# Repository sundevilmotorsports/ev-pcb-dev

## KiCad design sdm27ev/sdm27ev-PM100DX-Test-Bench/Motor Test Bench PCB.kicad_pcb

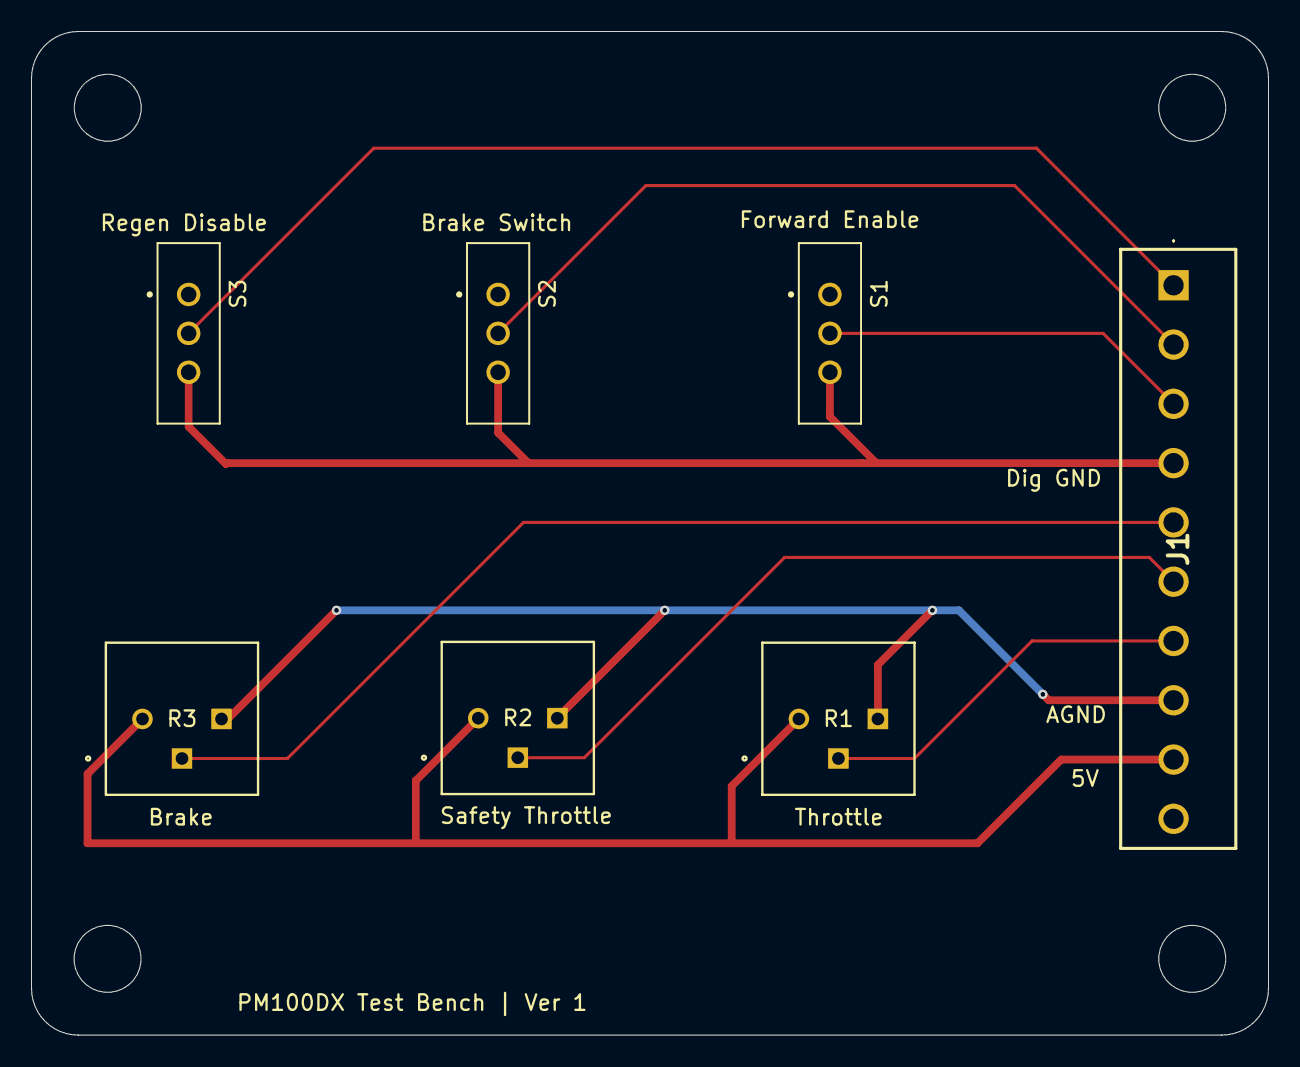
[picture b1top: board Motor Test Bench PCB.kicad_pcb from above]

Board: 2 copper layers, 79.5 x 64.5 mm, 7 parts (0 on the bottom side), 9 nets.

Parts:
J1: 20020327-D101B01LF; 20020327D101B01LF
R1: Throttle; POT_3386P
R2: Safety Throttle; POT_3386P
R3: Brake; POT_3386P
S1: Forward Enable; SW_EG1218
S2: Brake Switch; SW_EG1218
S3: Regen Disable; SW_EG1218

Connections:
5V: J1.9, R1.1, R2.1, R3.1
AGND: J1.8, R1.3, R2.3, R3.3
Brake Signal: J1.5, R3.2
Brake Switch: J1.2, S2.2
Digintal GND: J1.4, S1.3, S2.3, S3.3
Forward Enable: J1.3, S1.2
Regen Disable: J1.1, S3.2
Safety Throttle Signal: J1.6, R2.2
Throttle Signal: J1.7, R1.2

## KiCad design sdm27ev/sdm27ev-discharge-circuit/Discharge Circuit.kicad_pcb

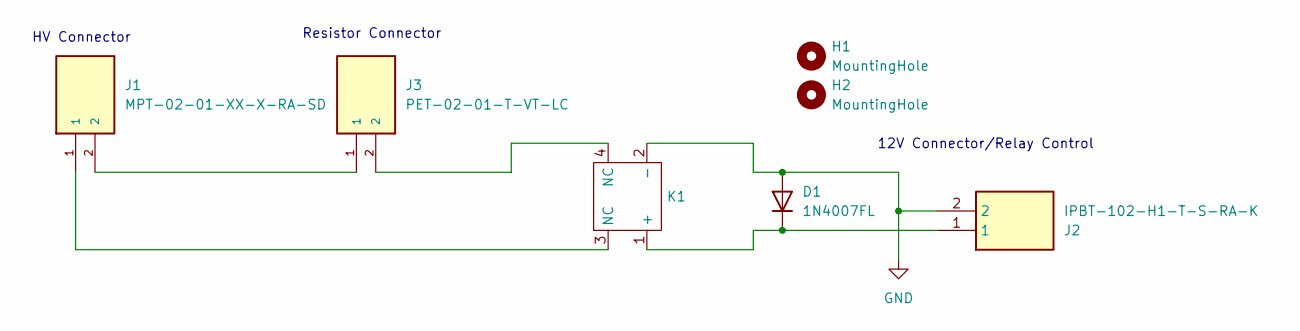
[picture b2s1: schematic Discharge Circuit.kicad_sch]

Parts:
D1: 1N4007FL; D_SOD-123F
H1, H2: MountingHole; MountingHole_3.2mm_M3
J1: MPT-02-01-XX-X-RA-SD; SAMTEC_MPT-02-01-XX-X-RA-SD; PARTREV B
J2: IPBT-102-H1-T-S-RA-K; IPBT102H1TSRAK; Mouser Part Number 200-IPBT102H1TSRAK
J3: PET-02-01-T-VT-LC; SAMTEC_PET-02-XX-X-VT-LC; PARTREV C
K1: S82405VHR

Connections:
GND: D1.2 (A), J2.2, K1.2 (-)
unnamed: D1.1 (K), J2.1, K1.1 (+)
unnamed: J1.1, K1.3 (NC)
unnamed: J1.2, J3.1
unnamed: J3.2, K1.4 (NC)

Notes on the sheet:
Resistor Connector
12V Connector/Relay Control
HV Connector

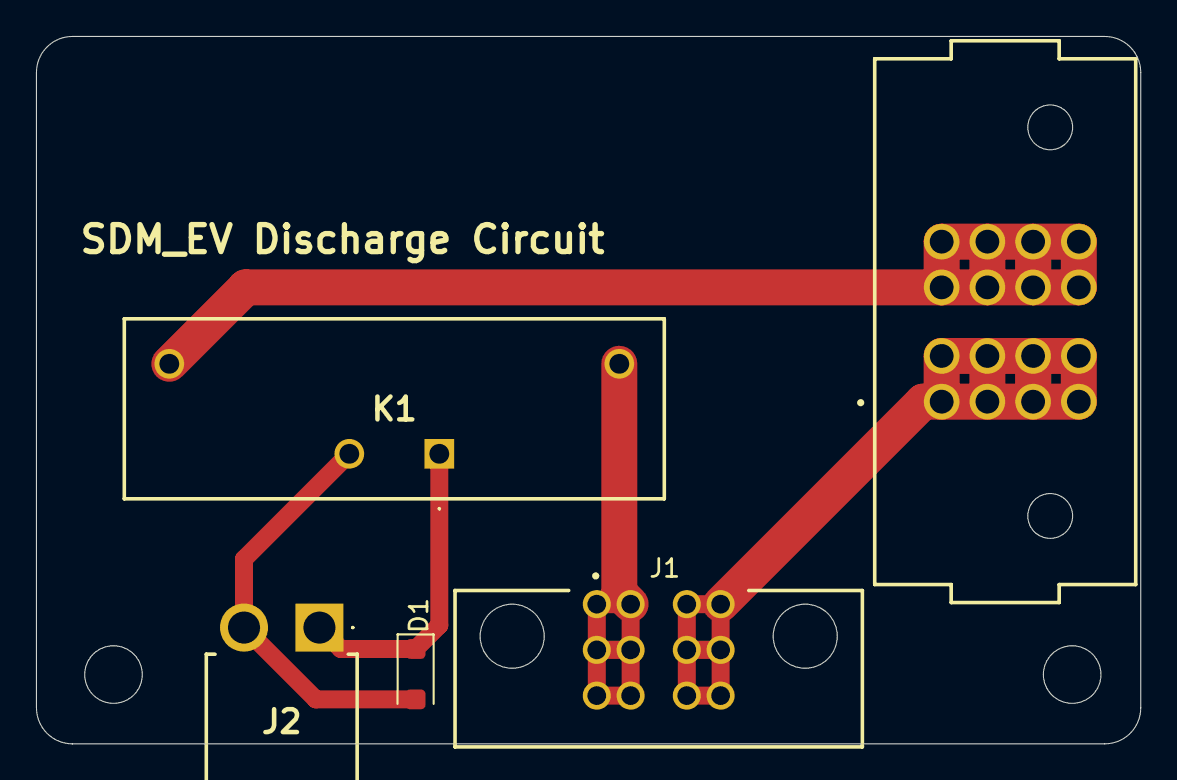
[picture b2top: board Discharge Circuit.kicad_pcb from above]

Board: 2 copper layers, 61.3 x 39.3 mm, 7 parts (0 on the bottom side), 5 nets.

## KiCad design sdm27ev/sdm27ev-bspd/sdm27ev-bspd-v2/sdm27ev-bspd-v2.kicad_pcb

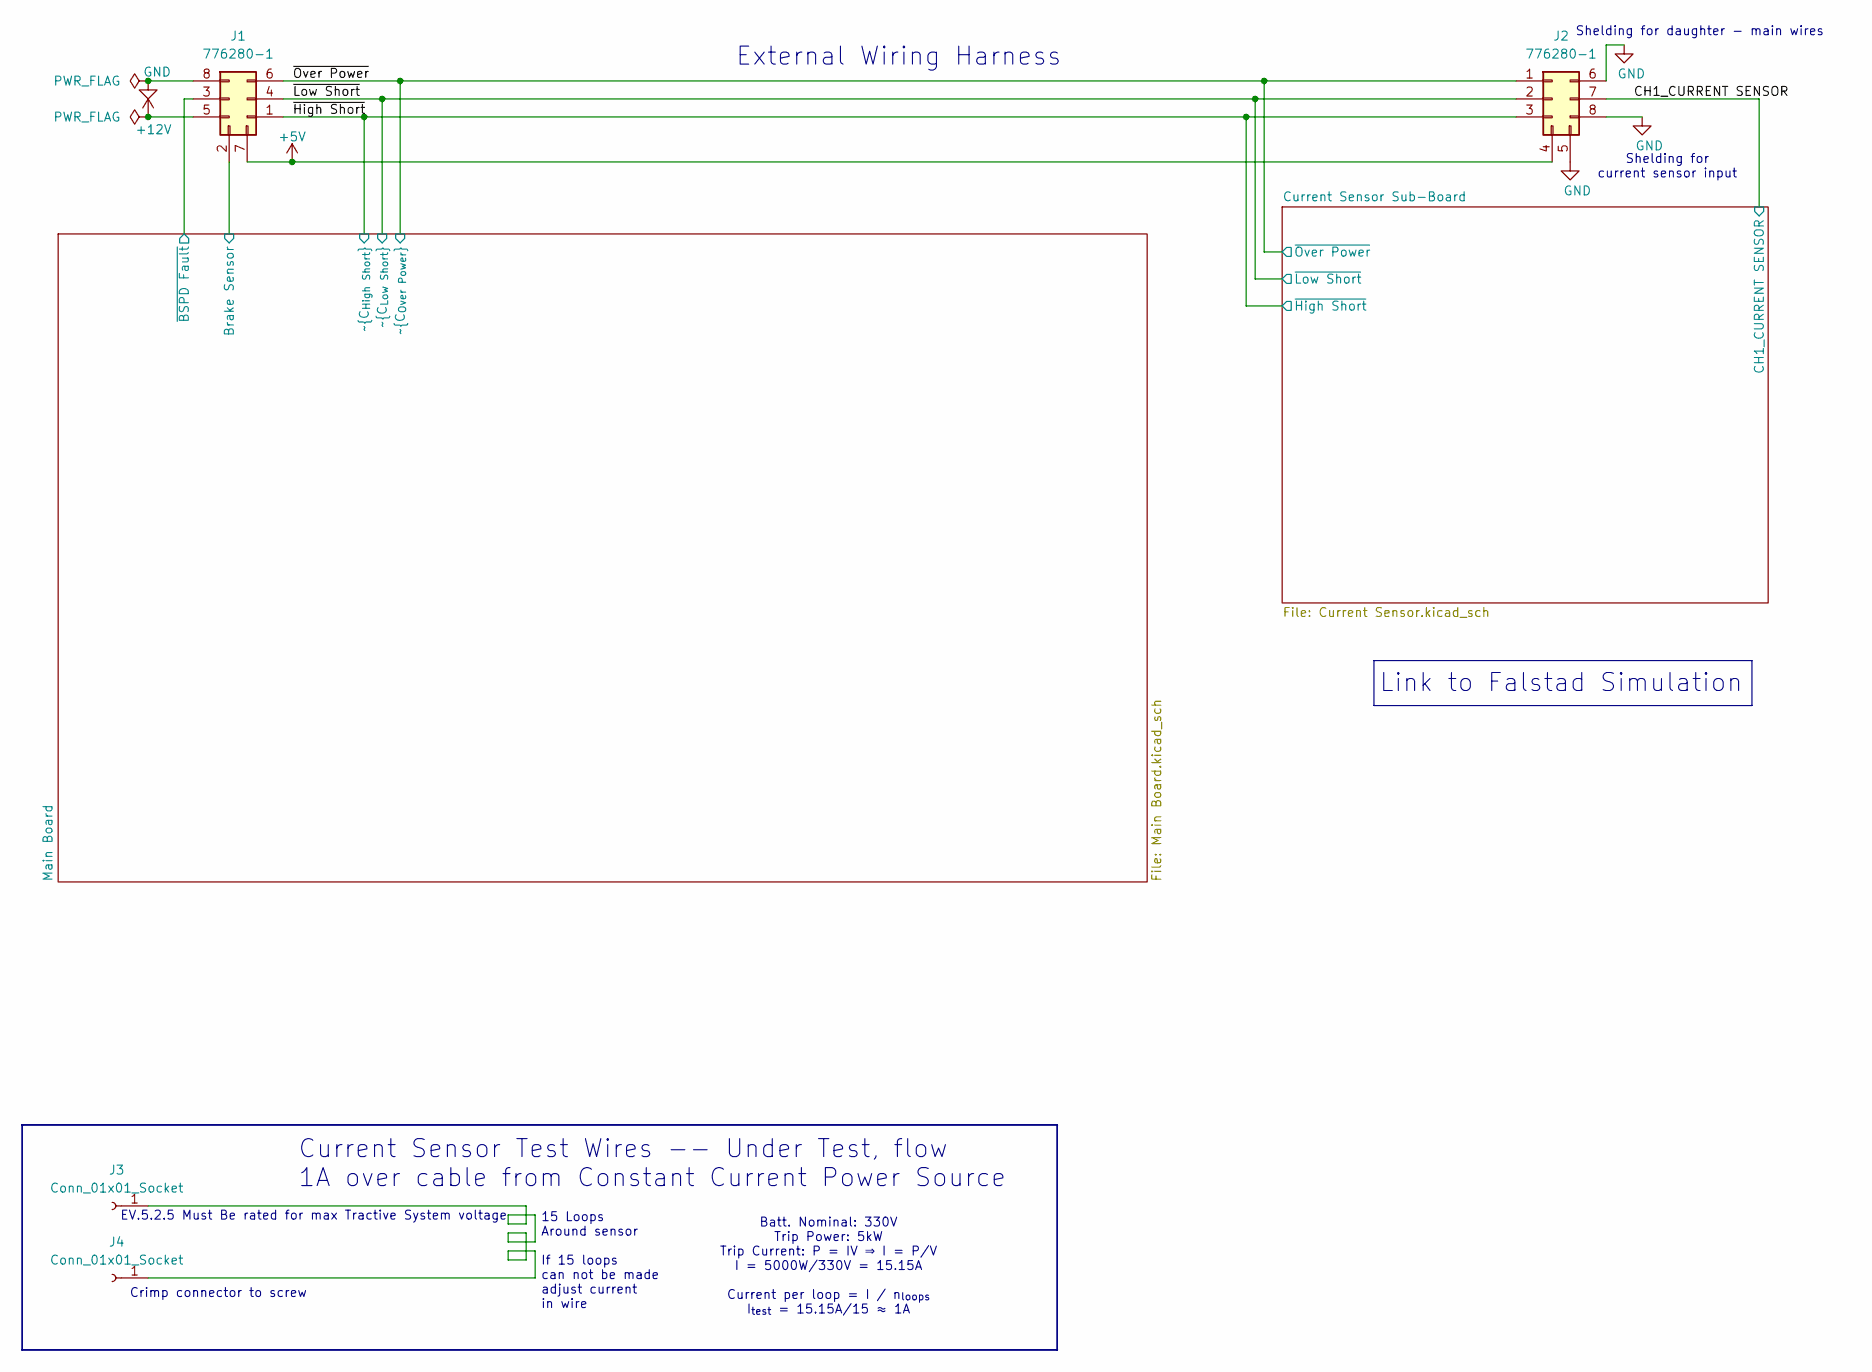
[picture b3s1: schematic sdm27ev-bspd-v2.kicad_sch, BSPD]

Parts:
J1, J2: 776280-1; Mouser Part Number 571-776280-1
J3, J4: Conn_01x01_Socket

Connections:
+5V: J1.7 (Pin_5), J2.4; also elsewhere on the board
+12V: J1.5 (Pin_3); also elsewhere on the board
/CH1_CURRENT SENSOR: J2.7; also elsewhere on the board
/Main Board/brake: J1.2 (Pin_4); also elsewhere on the board
/Main Board/~BSPD Fault: J1.3 (Pin_2); also elsewhere on the board
/~High Short: J1.1 (Pin_8), J2.3; also elsewhere on the board
/~Low Short: J1.4 (Pin_7), J2.2; also elsewhere on the board
/~Over Power: J1.6, J2.1; also elsewhere on the board
GND: J1.8 (Pin_1), J2.5, J2.6, J2.8; also elsewhere on the board
unnamed: J3.1, J4.1

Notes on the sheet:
External Wiring Harness
Batt. Nominal: 330V Trip Power: 5kW Trip Current: P = IV ⇒ I = P/V I = 5000W/330V = 15.15A Current per loop = I / n_{loops} I_{test} = 15.15A/15 ≈ 1A
15 Loops Around sensor If 15 loops can not be made adjust current in wire
Crimp connector to screw
EV.5.2.5 Must Be rated for max Tractive System voltage
Current Sensor Test Wires -- Under Test, flow 1A over cable from Constant Current Power Source
Shelding for daughter - main wires
Shelding for current sensor input
Link to Falstad Simulation

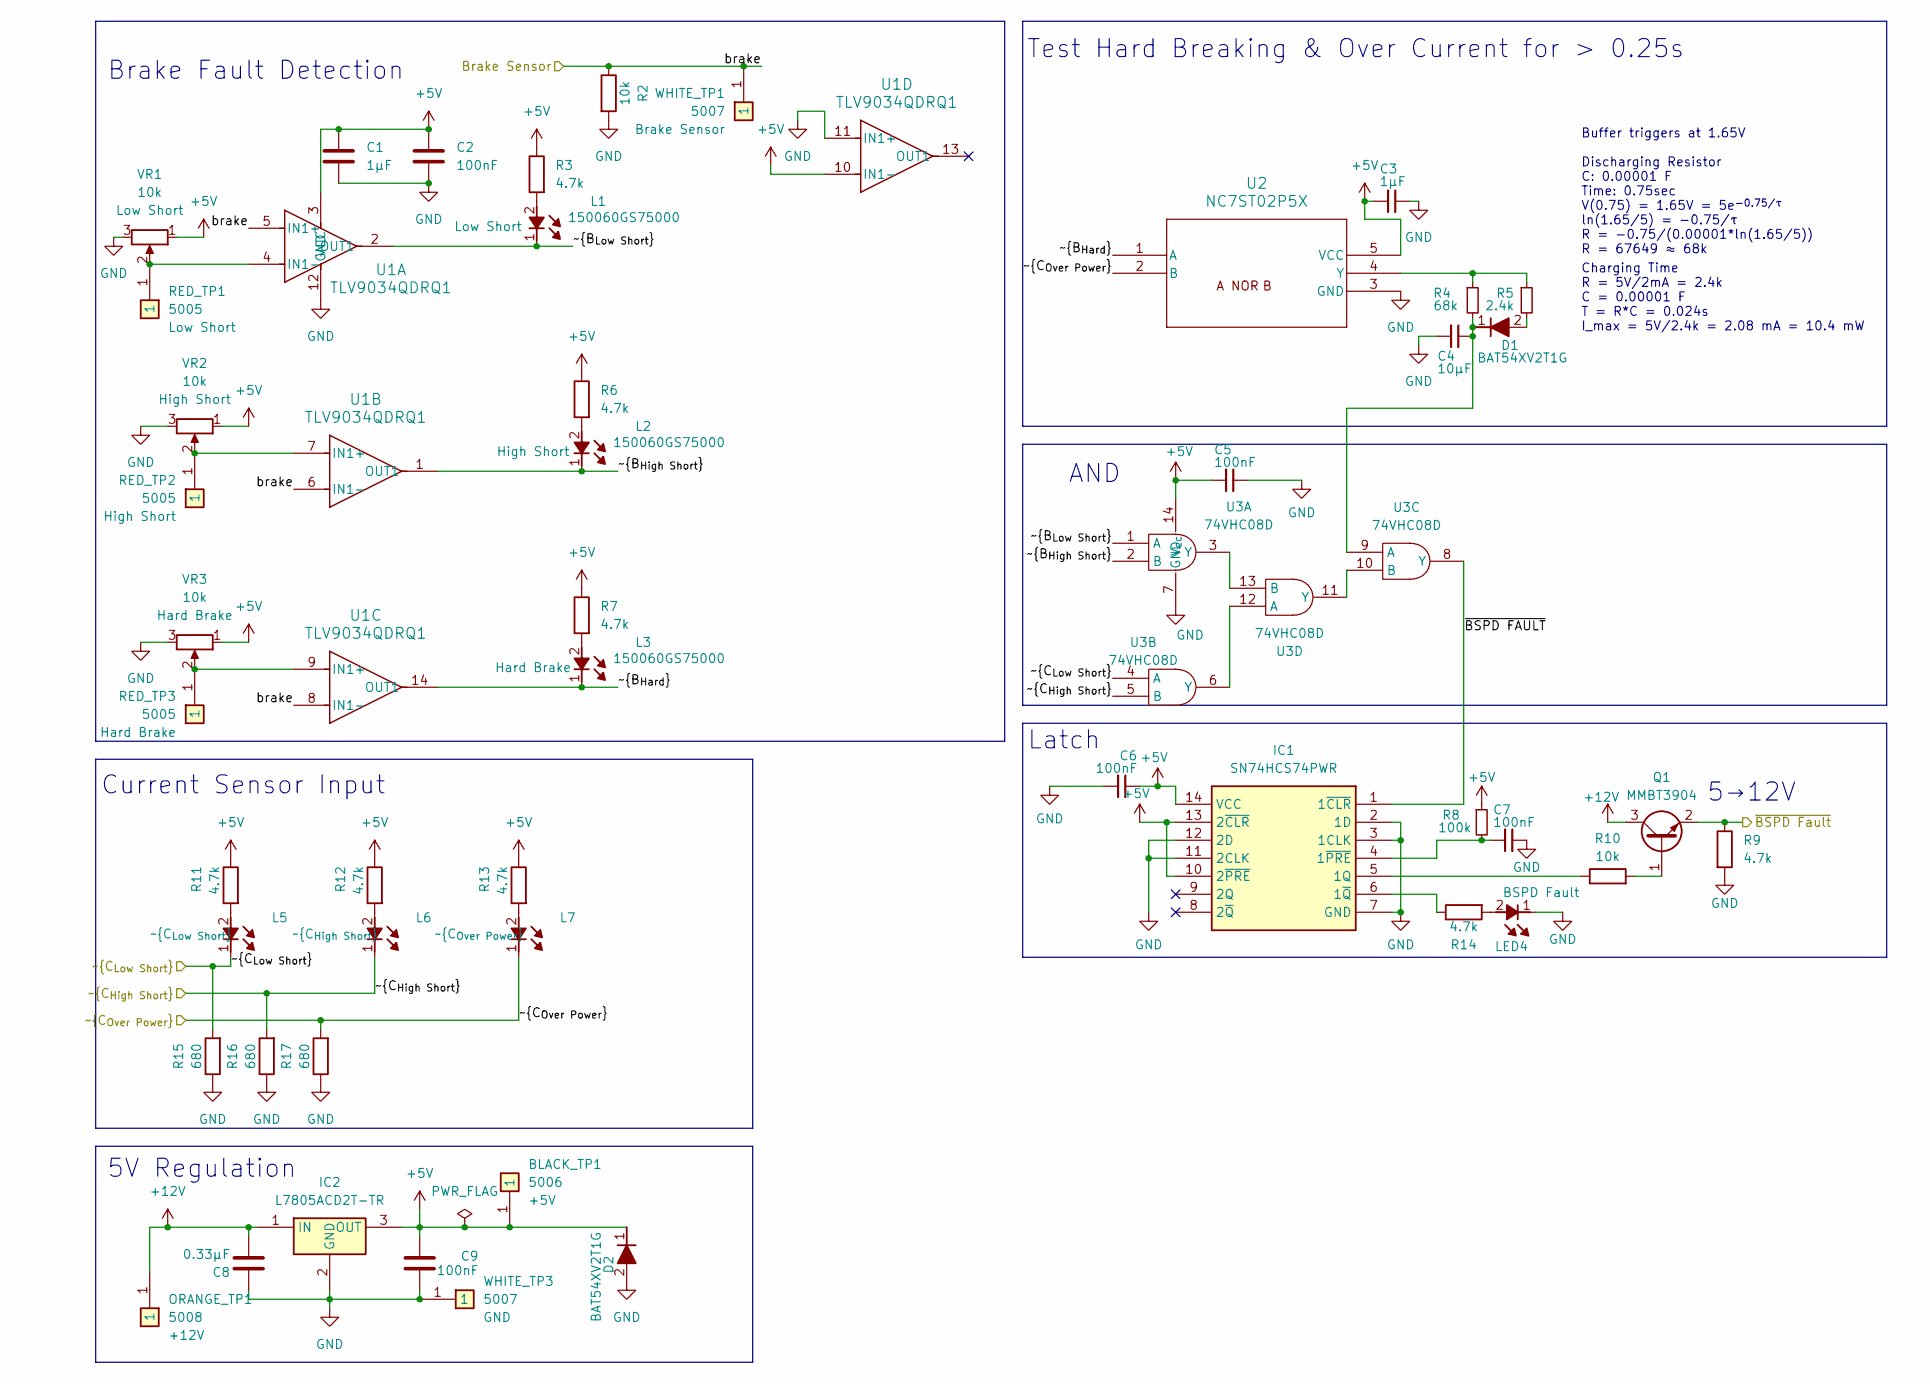
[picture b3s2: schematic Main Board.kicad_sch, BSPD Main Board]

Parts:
BLACK_TP1: 5006; Mouser Part Number 534-5006
C1, C3: 1µF; C_0603_1608Metric
C2, C5, C6, C7, C9: 100nF; C_0603_1608Metric
C4: 10µF; C_0603_1608Metric
C8: 0.33µF; C_0603_1608Metric
D1, D2: BAT54XV2T1G; SODFL1608X70N; Mouser Part Number 863-BAT54XV2T1G
IC1: SN74HCS74PWR; Mouser Part Number 595-SN74HCS74PWR
IC2: L7805ACD2T-TR; L7805ACD2TTR; Mouser Part Number 511-L7805ACD2T-TR
L1, L2, L3, L5, L6, L7: 150060GS75000; LEDC1608X80N; Mouser Part Number 710-150060GS75000
LED4: 150060GS75000; LEDC1608X80N; Mouser Part Number 710-150060GS75000
ORANGE_TP1: 5008; 5005; Mouser Part Number 534-5008
Q1: MMBT3904; SOT-23
R2, R10: 10k; R_0603_1608Metric
R3, R6, R7, R9, R11, R12, R13, R14: 4.7k; R_0603_1608Metric
R4: 68k; R_0603_1608Metric
R5: 2.4k; R_0603_1608Metric
R8: 100k; R_0603_1608Metric
R15, R16, R17: 680; R_0603_1608Metric
RED_TP1, RED_TP2, RED_TP3: 5005; Mouser Part Number 534-5005
U1: TLV9034QDRQ1; SOIC-14_3.9x8.7mm_P1.27mm
U2: NC7ST02P5X; SC-88A-5_1P35X2P2_ONS
U3: 74VHC08D
VR1, VR2, VR3: 10k; 3386P1103TLF; Mouser Part Number 652-3386P-1-103TLF
WHITE_TP1, WHITE_TP3: 5007; Mouser Part Number 534-5007

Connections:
+5V: BLACK_TP1.1 (1_1), C1.1, C2.1, C3.1, C5.2, C6.2, C9.2, D2.1 (K), IC1.10 (2~PRE), IC1.13 (2~CLR), IC1.14 (VCC), IC2.3 (OUT), R3.1, R6.1, R7.1, R8.1, R11.1, R12.1, R13.1, U1.3 (VCC), U1.10 (IN1-), U2.5 (VCC), U3.14 (V_{cc}), VR1.1 (CCW), VR2.1 (CCW), VR3.1 (CCW); also elsewhere on the board
+12V: C8.2, IC2.1 (IN), ORANGE_TP1.1 (1_1), Q1.3 (C); also elsewhere on the board
/Main Board/brake: R2.1, U1.5 (IN1+), U1.6 (IN1-), U1.8 (IN1-), WHITE_TP1.1 (1_1); also elsewhere on the board
/Main Board/~BSPD FAULT: IC1.1 (1~CLR), U3.8 (Y)
/Main Board/~BSPD Fault: Q1.2 (E), R9.1; also elsewhere on the board
/Main Board/~B_{Hard}: L3.1 (K), U1.14 (OUT1), U2.1 (A)
/Main Board/~B_{High Short}: L2.1 (K), U1.1 (OUT1), U3.2 (B)
/Main Board/~B_{Low Short}: L1.1 (K), U1.2 (OUT1), U3.1 (A)
/~High Short: L6.1 (K), R16.2, U3.5 (B); also elsewhere on the board
/~Low Short: L5.1 (K), R15.2, U3.4 (A); also elsewhere on the board
/~Over Power: L7.1 (K), R17.2, U2.2 (B); also elsewhere on the board
GND: C1.2, C2.2, C3.2, C4.2, C5.1, C6.1, C7.1, C8.1, C9.1, D2.2 (A), IC1.2 (1D), IC1.3 (1CLK), IC1.7 (GND), IC1.11 (2CLK), IC1.12 (2D), IC2.2 (GND), LED4.1 (K), R2.2, R9.2, R15.1, R16.1, R17.1, U1.11 (IN1+), U1.12 (GND), U2.3 (GND), U3.7 (GND), VR1.3 (CW), VR2.3 (CW), VR3.3 (CW), WHITE_TP3.1 (1_1); also elsewhere on the board
unnamed: D1.2 (A), R5.2
unnamed: C4.1, D1.1 (K), R4.2, U3.9 (A)
unnamed: IC1.5 (1Q), R10.1
unnamed: C7.2, IC1.4 (1~PRE), R8.2
unnamed: IC1.6 (1~Q), R14.1
unnamed: L1.2 (A), R3.2
unnamed: L2.2 (A), R6.2
unnamed: L3.2 (A), R7.2
unnamed: L5.2 (A), R11.2
unnamed: L6.2 (A), R12.2
unnamed: L7.2 (A), R13.2
unnamed: LED4.2 (A), R14.2
unnamed: Q1.1 (B), R10.2
unnamed: RED_TP1.1 (1_1), U1.4 (IN1-), VR1.2 (Wiper)
unnamed: RED_TP2.1 (1_1), U1.7 (IN1+), VR2.2 (Wiper)
unnamed: RED_TP3.1 (1_1), U1.9 (IN1+), VR3.2 (Wiper)
unnamed: R4.1, R5.1, U2.4 (Y)
unnamed: U3.3 (Y), U3.13 (B)
unnamed: U3.6 (Y), U3.12 (A)
unnamed: U3.10 (B), U3.11 (Y)

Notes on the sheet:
Brake Fault Detection
AND
Test Hard Breaking & Over Current for > 0.25s
5→12V
Current Sensor Input
Charging Time R = 5V/2mA = 2.4k C = 0.00001 F T = R*C = 0.024s I_max = 5V/2.4k = 2.08 mA = 10.4 mW
5V Regulation
Buffer triggers at 1.65V Discharging Resistor C: 0.00001 F Time: 0.75sec V(0.75) = 1.65V = 5e^{-0.75/τ} ln(1.65/5) = -0.75/τ R = -0.75/(0.00001*ln(1.65/5)) R = 67649 ≈ 68k
Latch

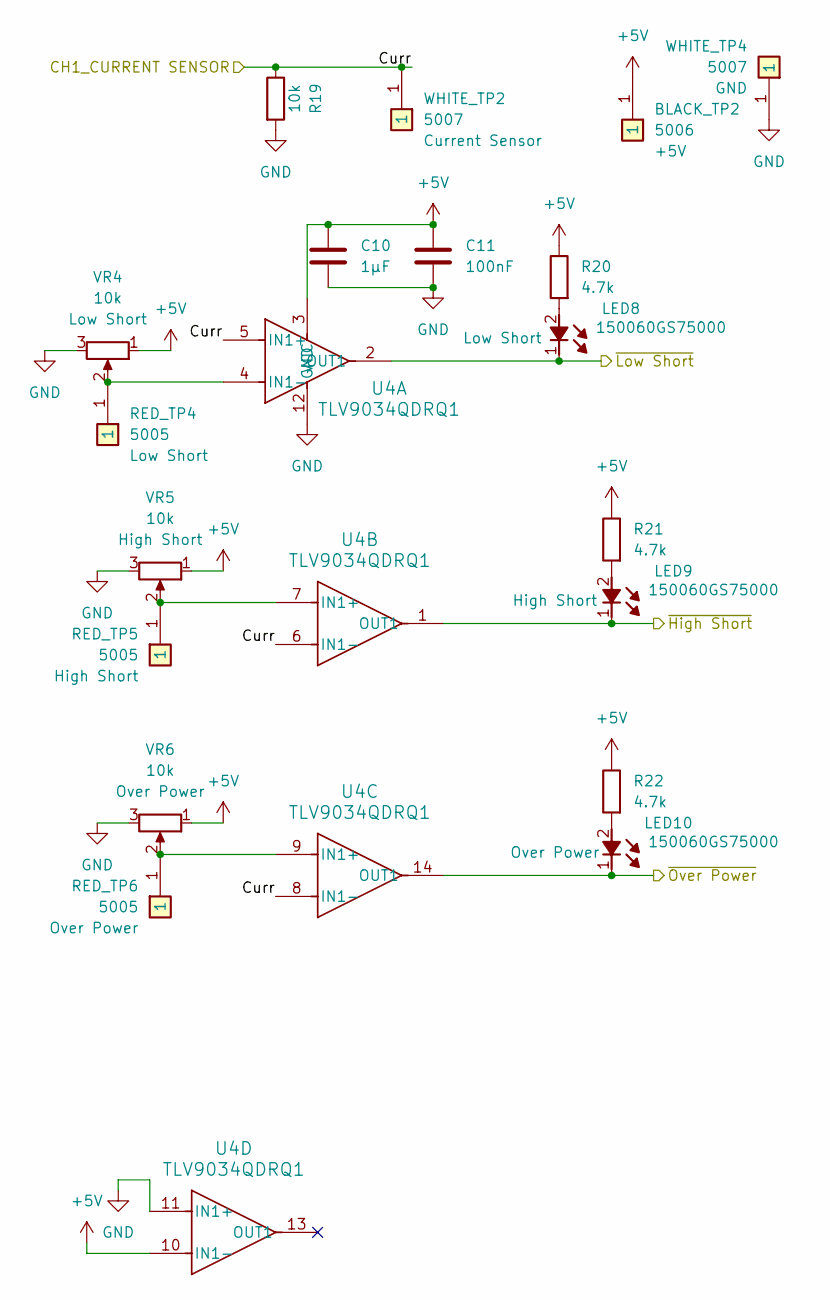
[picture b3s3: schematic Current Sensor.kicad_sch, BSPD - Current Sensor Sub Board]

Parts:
BLACK_TP2: 5006; Mouser Part Number 534-5006
C10: 1µF; C_0603_1608Metric
C11: 100nF; C_0603_1608Metric
LED8, LED9, LED10: 150060GS75000; LEDC1608X80N; Mouser Part Number 710-150060GS75000
R19: 10k; R_0603_1608Metric
R20, R21, R22: 4.7k; R_0603_1608Metric
RED_TP4, RED_TP5, RED_TP6: 5005; Mouser Part Number 534-5005
U4: TLV9034QDRQ1; SOIC-14_3.9x8.7mm_P1.27mm
VR4, VR5, VR6: 10k; 3386P1103TLF; Mouser Part Number 652-3386P-1-103TLF
WHITE_TP2, WHITE_TP4: 5007; Mouser Part Number 534-5007

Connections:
+5V: BLACK_TP2.1 (1_1), C10.1, C11.1, R20.1, R21.1, R22.1, U4.3 (VCC), U4.10 (IN1-), VR4.1 (CCW), VR5.1 (CCW), VR6.1 (CCW); also elsewhere on the board
/CH1_CURRENT SENSOR: R19.1, U4.5 (IN1+), U4.6 (IN1-), U4.8 (IN1-), WHITE_TP2.1 (1_1); also elsewhere on the board
/~High Short: LED9.1 (K), U4.1 (OUT1); also elsewhere on the board
/~Low Short: LED8.1 (K), U4.2 (OUT1); also elsewhere on the board
/~Over Power: LED10.1 (K), U4.14 (OUT1); also elsewhere on the board
GND: C10.2, C11.2, R19.2, U4.11 (IN1+), U4.12 (GND), VR4.3 (CW), VR5.3 (CW), VR6.3 (CW), WHITE_TP4.1 (1_1); also elsewhere on the board
unnamed: LED8.2 (A), R20.2
unnamed: LED9.2 (A), R21.2
unnamed: LED10.2 (A), R22.2
unnamed: RED_TP4.1 (1_1), U4.4 (IN1-), VR4.2 (Wiper)
unnamed: RED_TP5.1 (1_1), U4.7 (IN1+), VR5.2 (Wiper)
unnamed: RED_TP6.1 (1_1), U4.9 (IN1+), VR6.2 (Wiper)

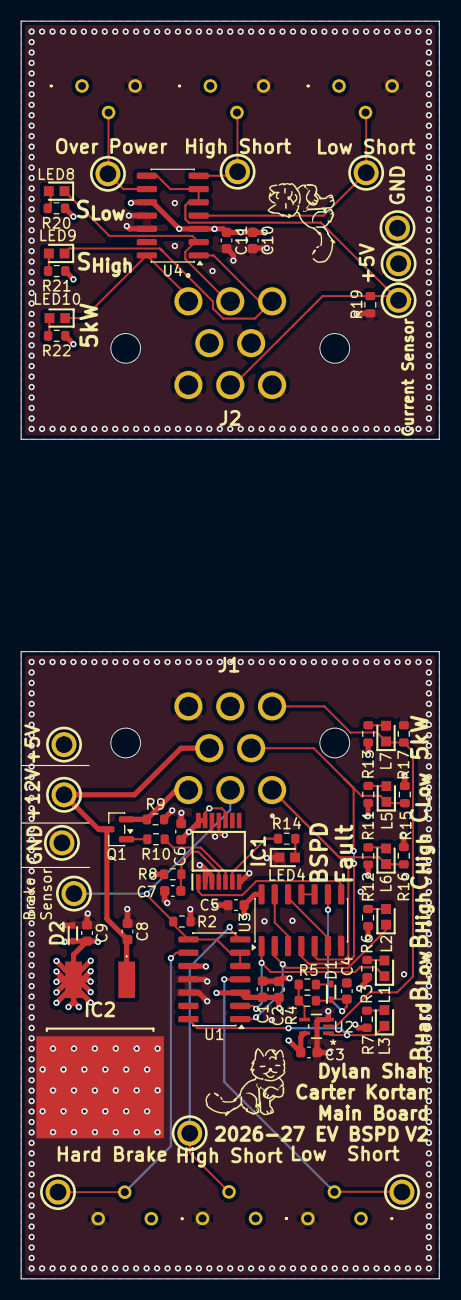
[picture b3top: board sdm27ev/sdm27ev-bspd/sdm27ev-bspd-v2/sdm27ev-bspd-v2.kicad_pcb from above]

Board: 4 copper layers, 40.0 x 120.3 mm, 71 parts (0 on the bottom side), 39 nets.

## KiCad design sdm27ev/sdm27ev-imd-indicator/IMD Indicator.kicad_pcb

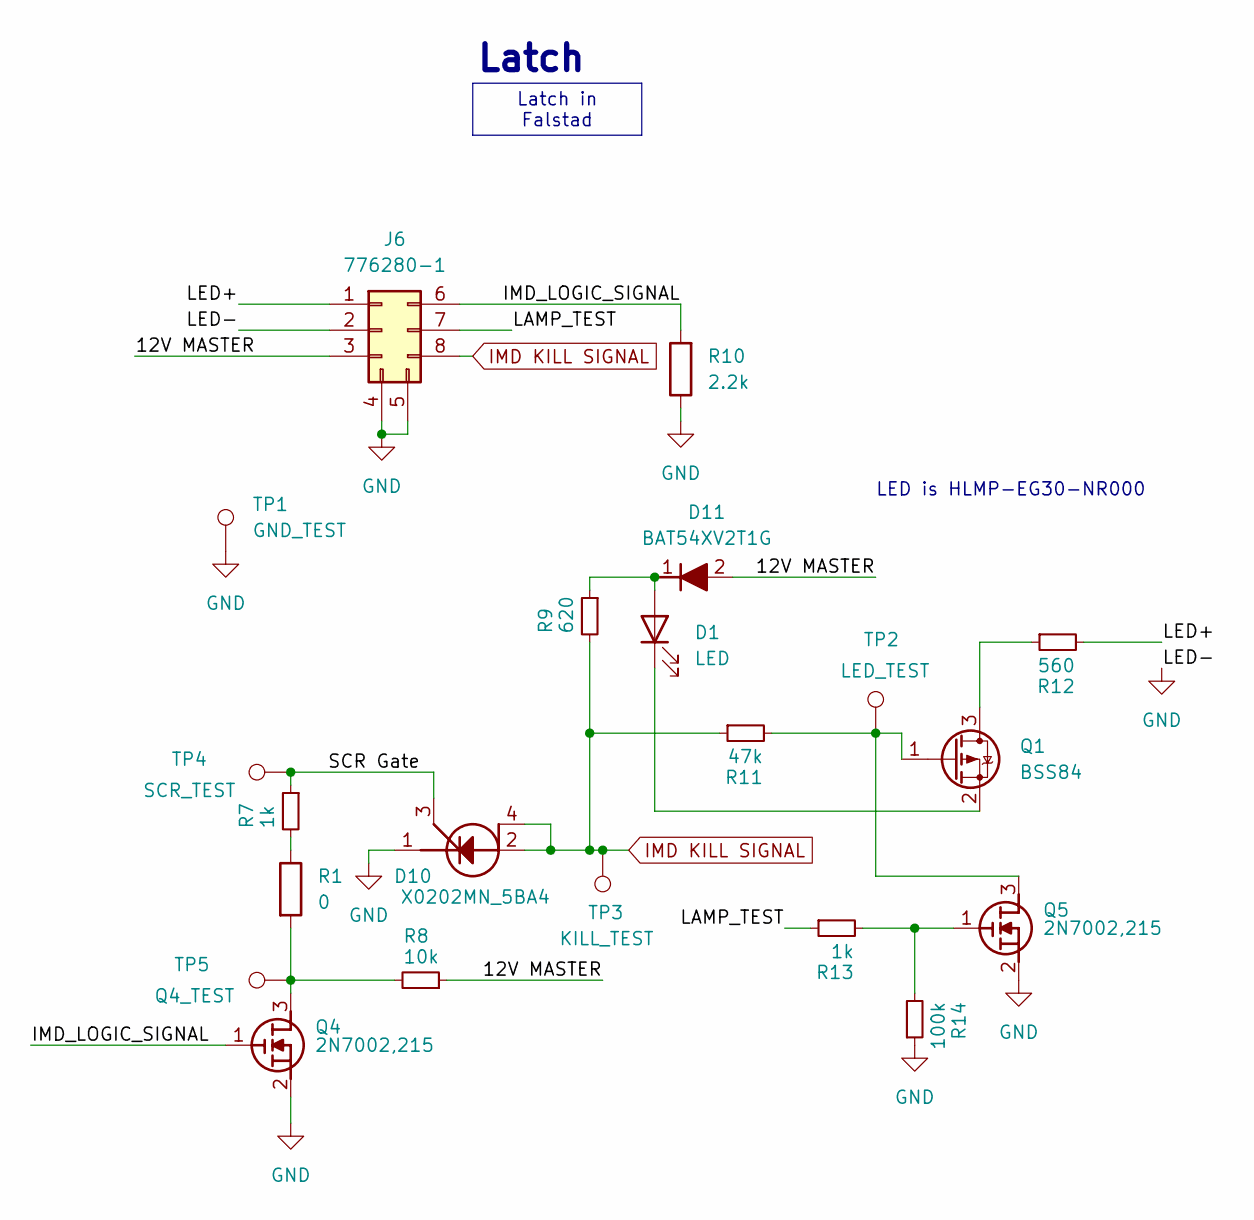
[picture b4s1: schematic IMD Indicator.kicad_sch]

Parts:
D1: LED; LED_0603_1608Metric
D10: X0202MN_5BA4; SOT230P700X190-4N; Mouser Part Number 511-X0202MN
D11: BAT54XV2T1G; SODFL1608X70N; Mouser Part Number 863-BAT54XV2T1G
J6: 776280-1; Mouser Part Number 571-776280-1
Q1: BSS84; SOT-23
Q4, Q5: 2N7002,215; SOT95P230X110-3N; Mouser Part Number 771-2N7002-T/R
R1: 0; R_0603_1608Metric
R7, R13: 1k; R_0603_1608Metric
R8: 10k; R_0603_1608Metric
R9: 620; R_0603_1608Metric
R10: 2.2k; R_0603_1608Metric
R11: 47k; R_0603_1608Metric
R12: 560; R_0603_1608Metric
R14: 100k; R_0603_1608Metric
TP1: GND_TEST; TestPoint_Pad_D1.5mm
TP2: LED_TEST; TestPoint_Pad_D1.5mm
TP3: KILL_TEST; TestPoint_Pad_D1.5mm
TP4: SCR_TEST; TestPoint_Pad_D1.5mm
TP5: Q4_TEST; TestPoint_Pad_D1.5mm

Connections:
/12V MASTER: D11.2 (A), J6.3, R8.1
/IMD_LOGIC_SIGNAL: J6.6, Q4.1 (G), R10.2
/LAMP_TEST: J6.7, R13.1
/LED+: J6.1, R12.2
/SCR Gate: D10.3 (G), R7.1, TP4.1 (1_1)
GND: D10.1 (K), J6.2, J6.4, J6.5, Q4.2 (S), Q5.2 (S), R10.1, R14.1, TP1.1 (1_1)
IMD KILL SIGNAL: D10.2 (A_1), D10.4 (A_2), J6.8, R9.2, R11.1, TP3.1 (1_1)
unnamed: D1.2 (A), D11.1 (K), R9.1
unnamed: D1.1 (K), Q1.2 (S)
unnamed: Q1.3 (D), R12.1
unnamed: Q1.1 (G), Q5.3 (D), R11.2, TP2.1 (1_1)
unnamed: Q4.3 (D), R1.2, R8.2, TP5.1 (1_1)
unnamed: Q5.1 (G), R13.2, R14.2
unnamed: R1.1, R7.2

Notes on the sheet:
Latch
LED is HLMP-EG30-NR000
Latch in Falstad

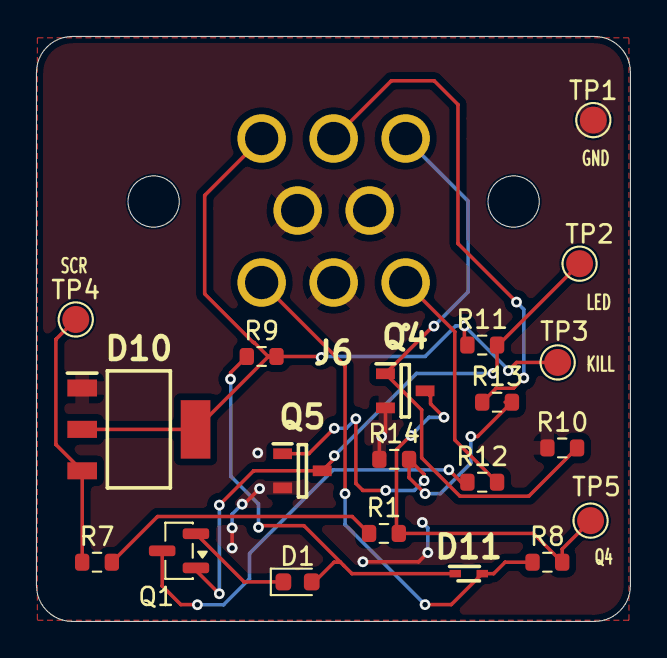
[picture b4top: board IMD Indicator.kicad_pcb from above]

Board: 2 copper layers, 33.0 x 32.5 mm, 21 parts (0 on the bottom side), 14 nets.

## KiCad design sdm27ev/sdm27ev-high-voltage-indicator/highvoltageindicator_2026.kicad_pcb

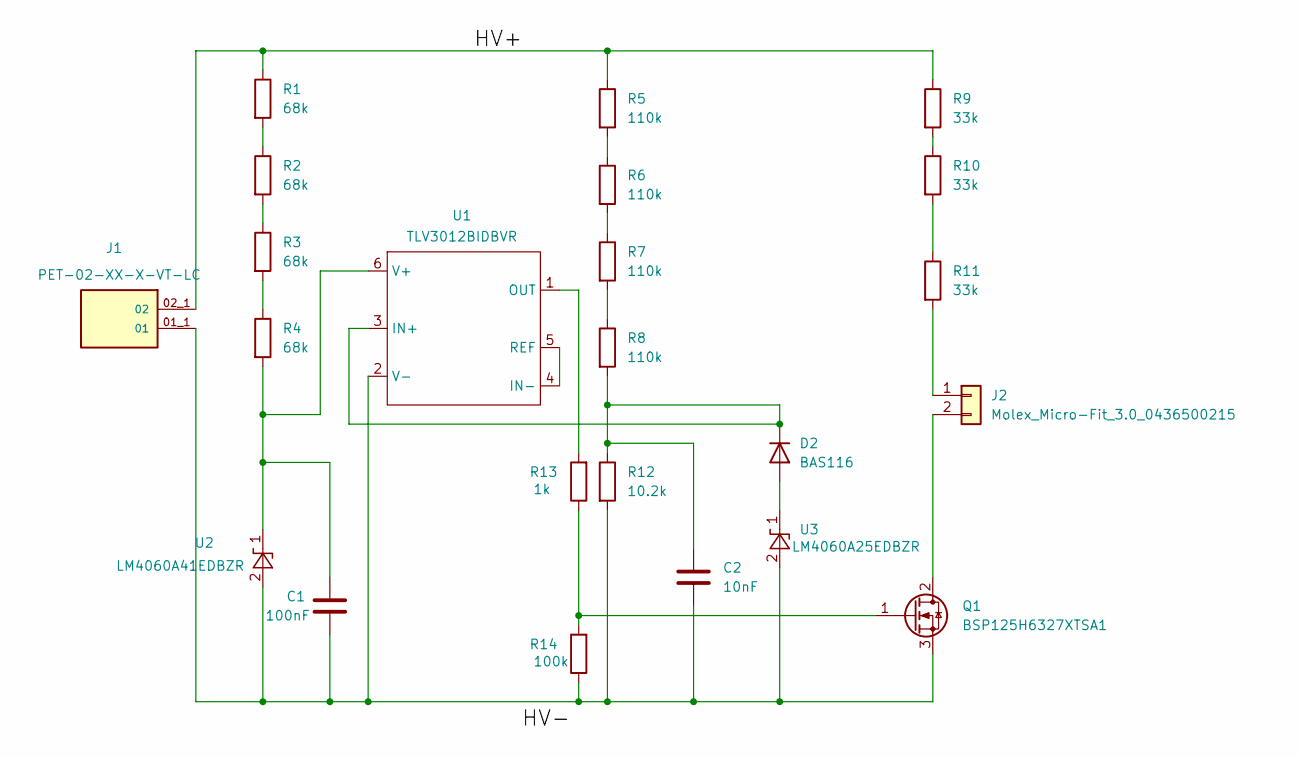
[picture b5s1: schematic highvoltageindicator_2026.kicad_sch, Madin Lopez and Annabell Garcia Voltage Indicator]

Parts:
C1: 100nF; C_1206_3216Metric
C2: 10nF; C_1206_3216Metric
D2: BAS116; SOT-23
J1: PET-02-XX-X-VT-LC; SAMTEC_PET-02-XX-X-VT-LC; PARTREV C
J2: Molex_Micro-Fit_3.0_0436500215; Molex_Micro-Fit_3.0_43650-0215_1x02_P3.00mm_Vertical
Q1: BSP125H6327XTSA1; SOT-223-3_TabPin2
R1, R2, R3, R4: 68k; R_2512_6332Metric
R5, R6, R7, R8: 110k; R_1206_3216Metric
R9, R10, R11: 33k; R_2512_6332Metric
R12: 10.2k; R_1206_3216Metric
R13: 1k; R_1206_3216Metric
R14: 100k; R_1206_3216Metric
U1: TLV3012BIDBVR; SOT-23-6
U2: LM4060A41EDBZR; SOT-23
U3: LM4060A25EDBZR; SOT-23

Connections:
/HV+: J1.02_1 (02), R1.1, R5.1, R9.1
unnamed: D2.2 (A), U3.1 (K)
unnamed: C2.1, D2.1 (K), R8.2, R12.1, U1.3 (IN+)
unnamed: C1.2, C2.2, J1.01_1 (01), Q1.3 (S), R12.2, R14.1, U1.2 (V-), U2.2 (A), U3.2 (A)
unnamed: J2.1, R11.2
unnamed: J2.2, Q1.2 (D)
unnamed: Q1.1 (G), R13.1, R14.2
unnamed: R1.2, R2.1
unnamed: R2.2, R3.1
unnamed: R3.2, R4.1
unnamed: R5.2, R6.1
unnamed: R6.2, R7.1
unnamed: R7.2, R8.1
unnamed: R9.2, R10.1
unnamed: R10.2, R11.1
unnamed: U1.4 (IN-), U1.5 (REF)
unnamed: R13.2, U1.1 (OUT)
unnamed: C1.1, R4.2, U1.6 (V+), U2.1 (K)

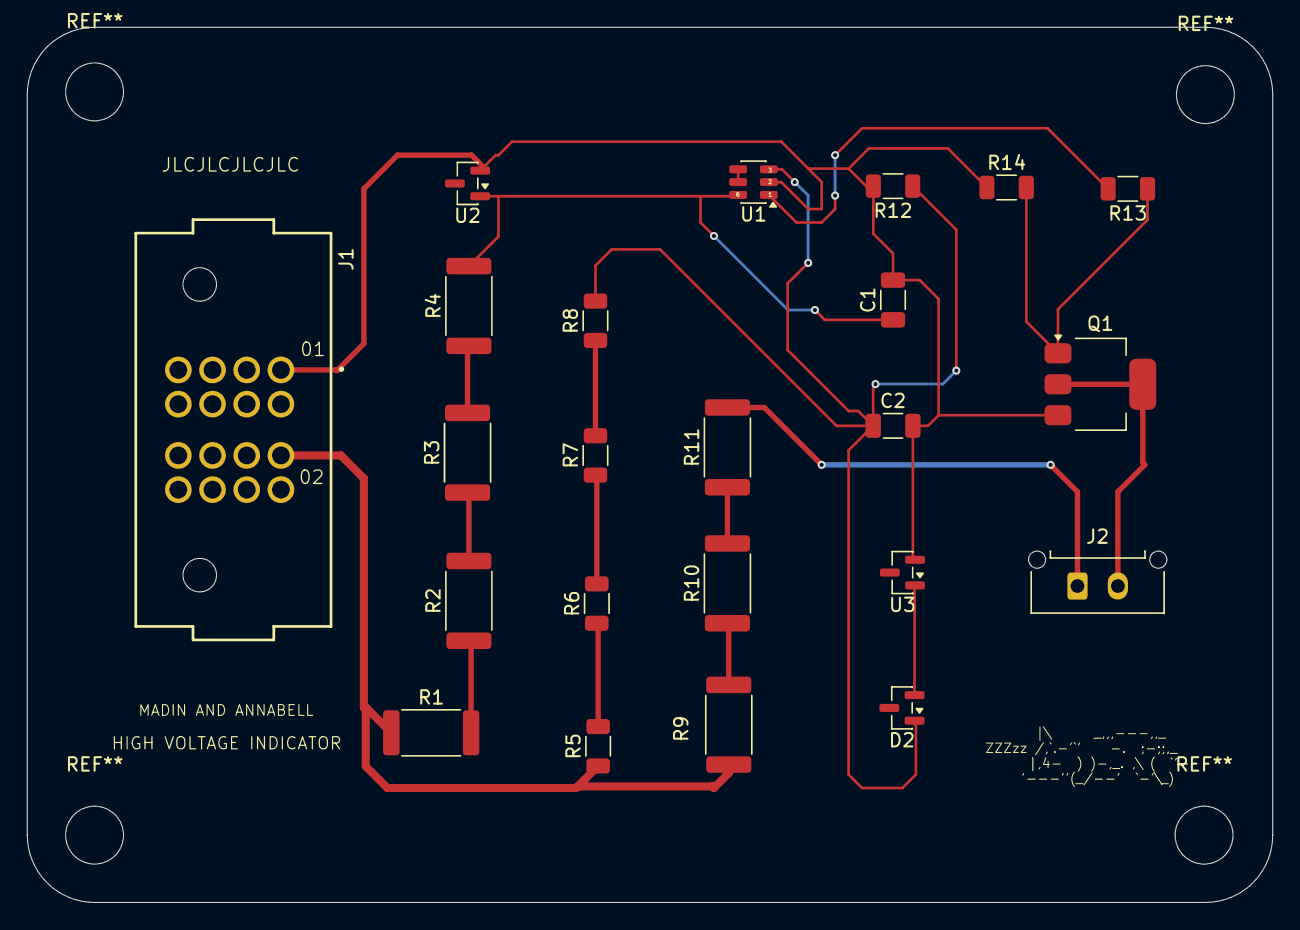
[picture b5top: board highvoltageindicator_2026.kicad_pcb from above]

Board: 4 copper layers, 92.5 x 65.0 mm, 23 parts (0 on the bottom side), 18 nets.
